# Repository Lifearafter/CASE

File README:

# C.A.S.E

Welcome to the Compact Antenna Experimenter System Project repository! This project focuses on providing the necessary code and documentation to create a fully functional and electrically viable CubeSat. In this repository, you will find the software and firmware that drive the electrical components of a CubeSat, ensuring its proper functionality in space.

## Table of Contents

- Introduction
- Getting Started
- Project Structure
- Dependencies
- Contributing
- License

## Introduction

CubeSats are miniaturized satellites that have become increasingly popular for space exploration and scientific research due to their small size, cost-effectiveness, and modular design. This project focuses specifically on the electrical aspects of a CubeSat, excluding any mechanical components.

The key objectives of this project include:

- **Power Management:** Efficiently manage power resources to ensure the CubeSat's continuous operation in space.

- **Communication Systems:** Implement reliable communication protocols for data transmission between the CubeSat and ground control.

- **Sensor Integration:** Integrate and interface various sensors to gather data for scientific or mission-specific purposes.

- **Onboard Computer Systems:** Develop the necessary software for the CubeSat's onboard computer to execute mission tasks and handle data.

- **Fault Tolerance:** Implement mechanisms to handle errors and faults to ensure the CubeSat's robustness in harsh space environments.

## Getting Started

To get started with the CubeSatellite Electrical System Project, follow these steps:

1. **Clone the Repository:**

```
bash
Copy code
git clone https://github.com/your-username/cubesatellite-electrical.git
```

2. **Navigate to the Project Directory:**

```
bash
Copy code
cd cubesatellite-electrical
```

## Explore the Code:

Review the codebase to understand the implementation details and structure.

## Set Up Development Environment:

Follow the instructions in the docs/setup.md document to set up your development environment.

## Contribute:

If you would like to contribute to the project, please follow the guidelines outlined in the Contributing section.

## Project Structure

The project is organized into the following directories:

- src: Contains the source code for the CubeSat's electrical systems.
- docs: Documentation files, including setup instructions and usage guidelines.
- tests: Test cases for ensuring the reliability and functionality of the code.
- inc: Contains all the header files for the project.

## Dependencies

Ensure that you have the following dependencies installed in your development environment:
**Not yet listed**

## License

This project is licensed under the MIT License. Feel free to use, modify, and distribute the code for your CubeSat projects.

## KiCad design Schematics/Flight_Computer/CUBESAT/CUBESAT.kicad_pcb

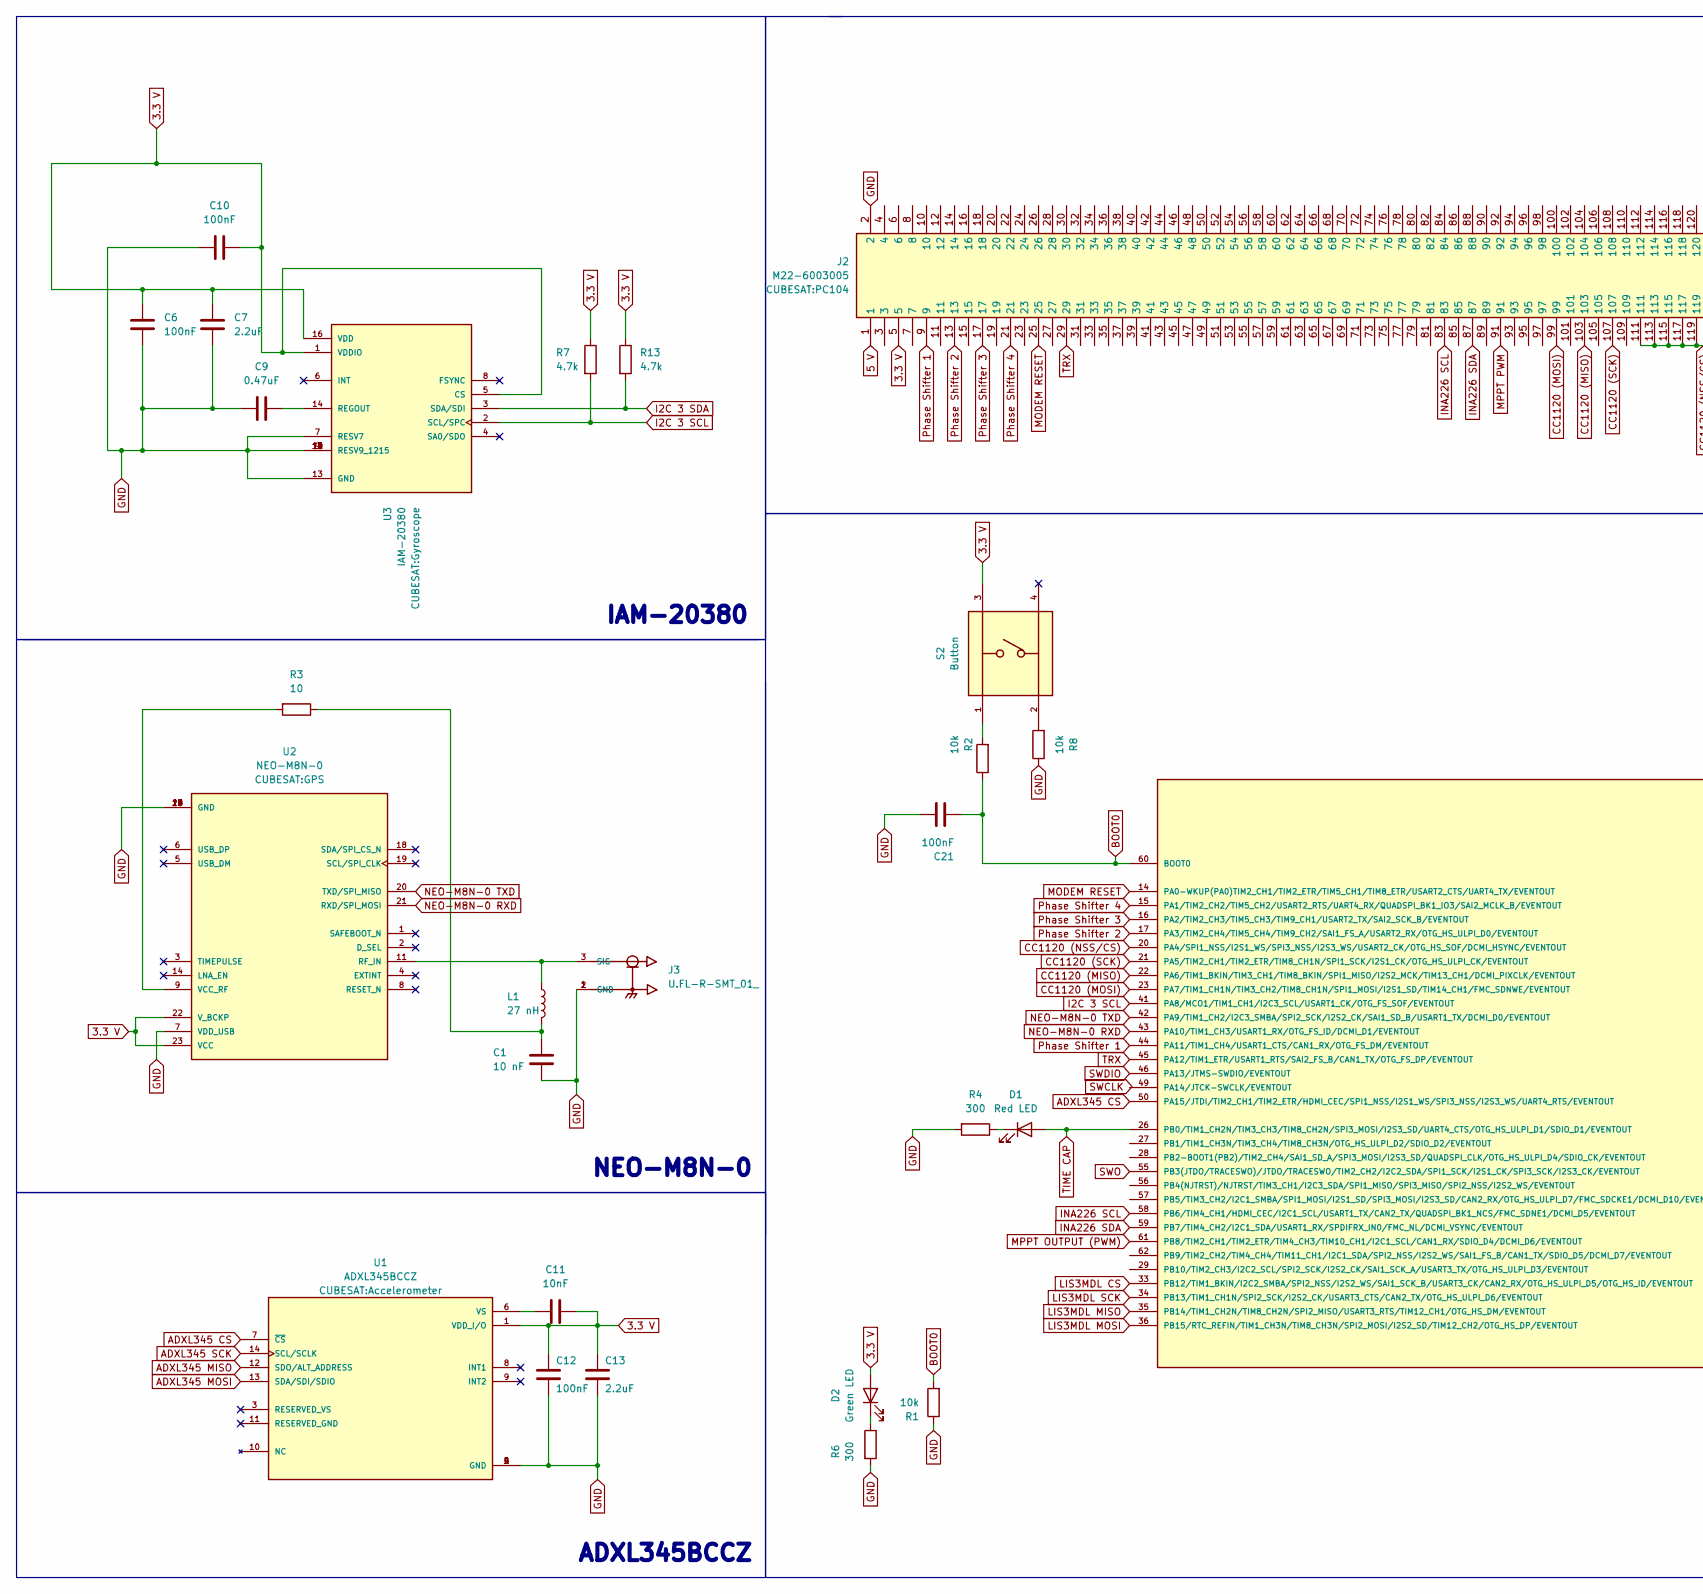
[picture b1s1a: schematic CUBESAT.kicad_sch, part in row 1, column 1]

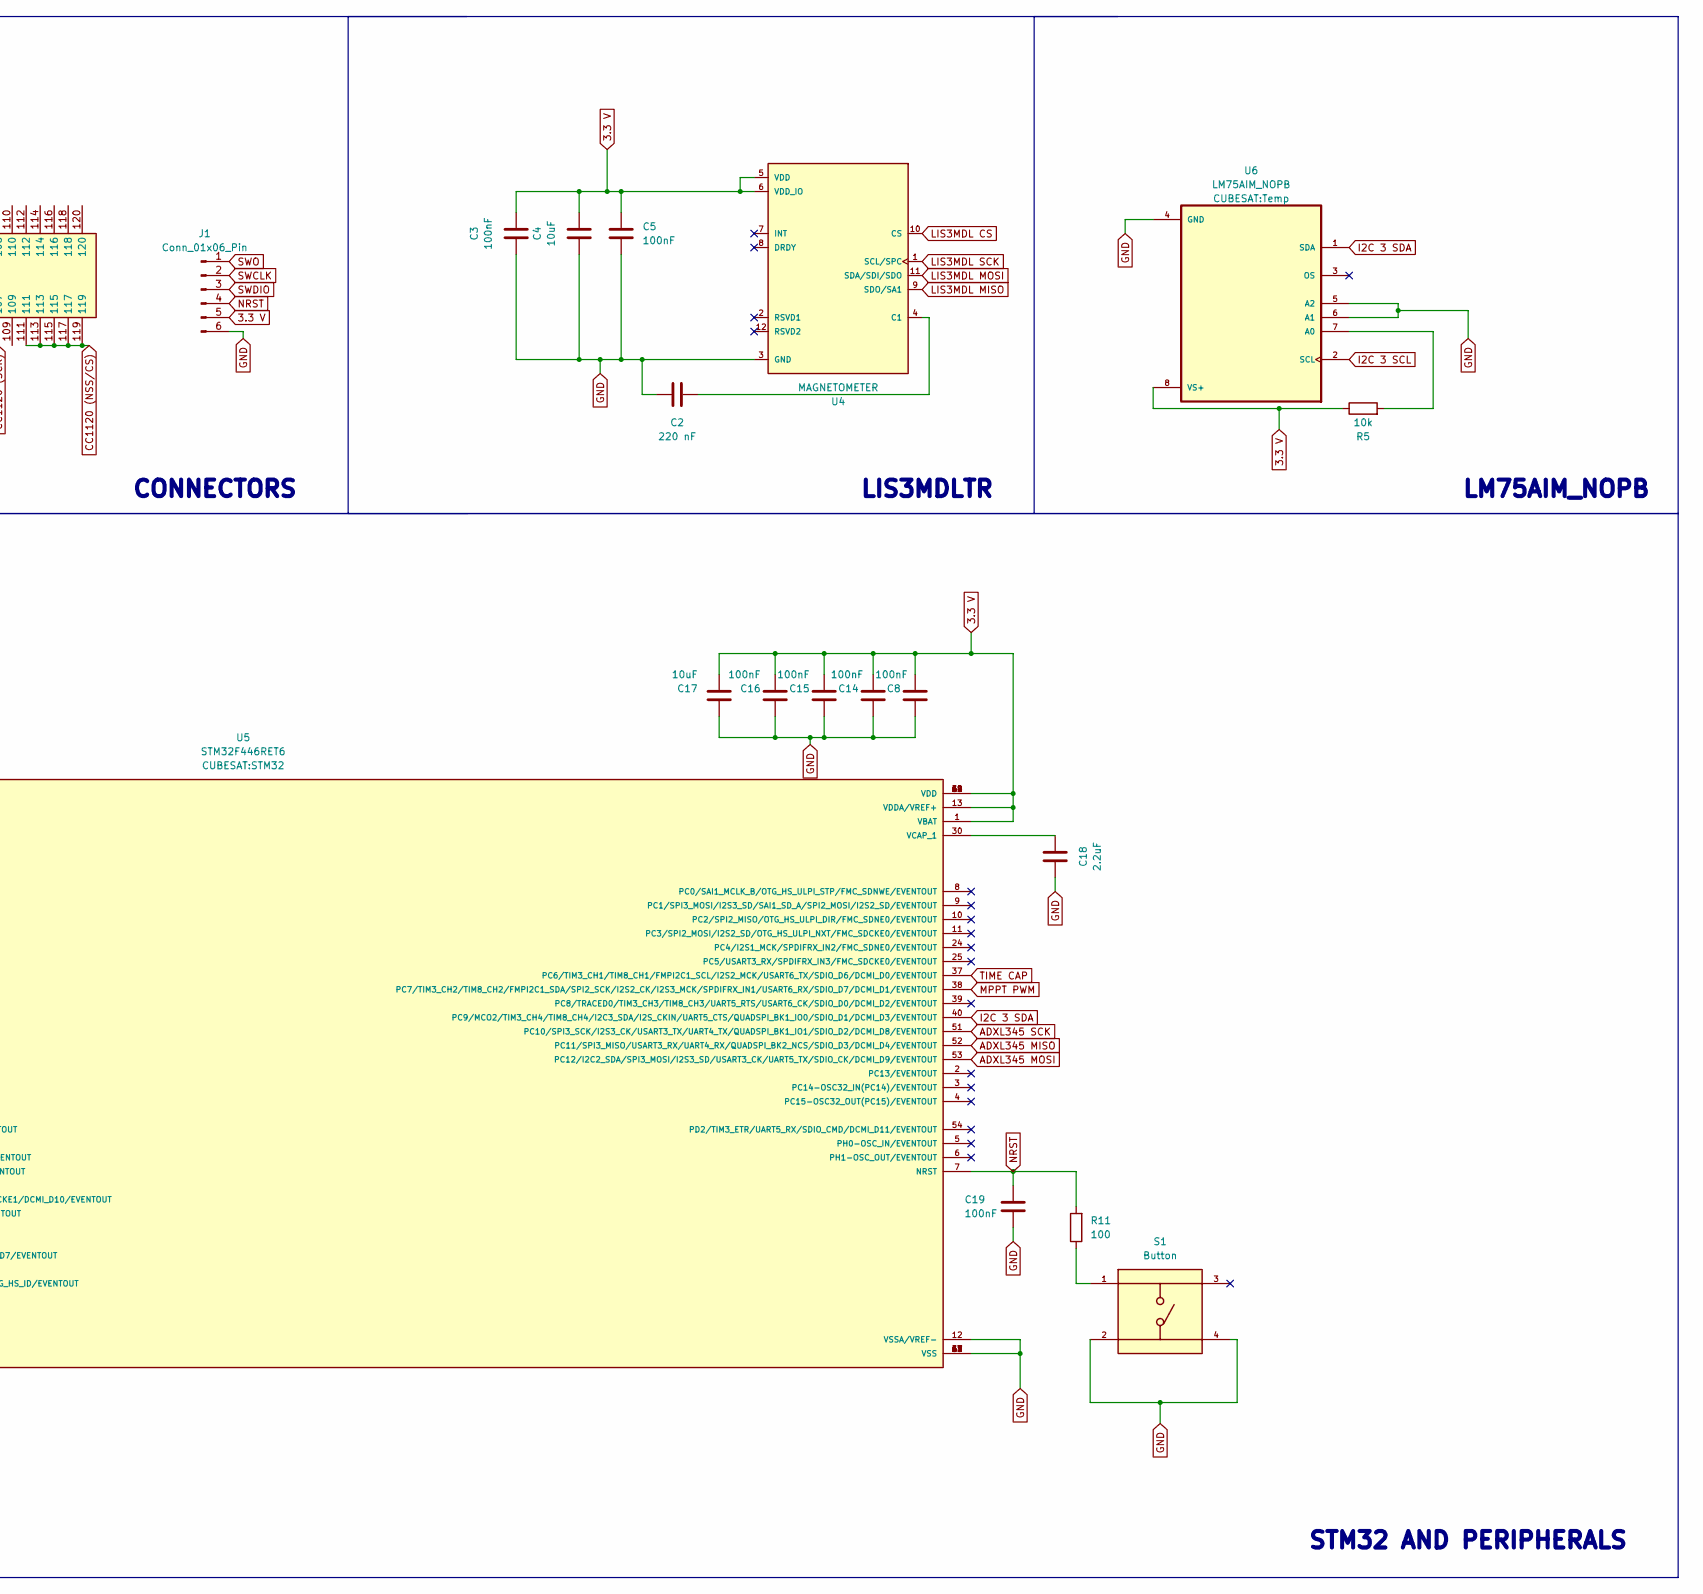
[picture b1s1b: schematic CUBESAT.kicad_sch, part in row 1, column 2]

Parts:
C1: 10 nF; Capacitor10nf
C2: 220 nF; Capacitor220nf
C3, C5, C6, C8, C10, C12, C14, C15, C16, C19, C21: 100nF; Capacitor100nf
C4, C17: 10uF; Capacitor10uf
C7, C13, C18: 2.2uF; Capacitor2-2uf
C9: 0.47uF; Capacitor0-47uf
C11: 10nF; Capacitor10nf
D1: Red LED
D2: Green LED
J1: Conn_01x06_Pin; 6 Pin Connector
J2: M22-6003005; PC104; Manufacturer_Part_Number M22-6003005
J3: U.FL-R-SMT_01_; UFL
L1: 27 nH; Inductor27nH
R1, R2, R5, R8: 10k; Resistor10kO
R3: 10; Resistor10O
R4, R6: 300; Resistor300O
R7, R13: 4.7k; Resistor4.7kO
R11: 100; Reistor100O
S1, S2: Button
U1: ADXL345BCCZ; Accelerometer; PARTREV G
U2: NEO-M8N-0; GPS; PARTREV R04
U3: IAM-20380; Gyroscope
U4: MAGNETOMETER
U5: STM32F446RET6; STM32; PARTREV 6
U6: LM75AIM_NOPB; Temp

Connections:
3.3 V: C3.2, C4.2, C5.2, C6.1, C7.1, C8.1, C10.2, C11.2, C12.1, C13.1, C14.1, C15.1, C16.1, C17.1, D2.2 (A), J1.5, J2.5, R5.1, R7.1, R13.1, S2.3, U1.1 (VDD_I/O), U2.22 (V_BCKP), U2.23 (VCC), U3.1 (VDDIO), U3.5 (CS), U3.16 (VDD), U4.5 (VDD), U4.6 (VDD_IO), U5.1 (VBAT), U5.13 (VDDA/VREF+), U5.19 (VDD), U5.32 (VDD), U5.48 (VDD), U5.64 (VDD), U6.8 (VS+)
5 V: J2.1
ADXL345 CS: U1.7 (~CS), U5.50 (PA15/JTDI/TIM2_CH1/TIM2_ETR/HDMI_CEC/SP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)
ADXL345 MISO: U1.12 (SDO/ALT_ADDRESS), U5.52 (PC11/SPI3_MISO/USART3_RX/UART4_RX/QUADS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)
ADXL345 MOSI: U1.13 (SDA/SDI/SDIO), U5.53 (PC12/I2C2_SDA/SPI3_MOSI/I2S3_SD/USART3_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)
ADXL345 SCK: U1.14 (SCL/SCLK), U5.51 (PC10/SPI3_SCK/I2S3_CK/USART3_TX/UART4_T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)
BOOT0: C21.2, R1.2, R2.1, U5.60 (BOOT0)
CC1120 (MISO): J2.103, U5.22 (PA6/TIM1_BKIN/TIM3_CH1/TIM8_BKIN/SPI1_M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)
CC1120 (MOSI): J2.99, U5.23 (PA7/TIM1_CH1N/TIM3_CH2/TIM8_CH1N/SPI1_M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)
CC1120 (NSS/CS): J2.111, J2.113, J2.115, J2.117, J2.119, U5.20 (PA4/SPI1_NSS/I2S1_WS/SPI3_NSS/I2S3_WS/U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)
CC1120 (SCK): J2.107, U5.21 (PA5/TIM2_CH1/TIM2_ETR/TIM8_CH1N/SPI1_SC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)
GND: C1.2, C2.1, C3.1, C4.1, C5.1, C6.2, C7.2, C8.2, C9.2, C10.1, C12.2, C13.2, C14.2, C15.2, C16.2, C17.2, C18.1, C19.2, C21.1, J1.6, J2.2, J3.1 (GND), J3.2 (GND), R1.1, R4.2, R6.2, R8.1, S1.2, S1.4, U1.2 (GND), U1.4 (GND), U1.5 (GND), U2.7 (VDD_USB), U2.10 (GND), U2.12 (GND), U2.13 (GND), U2.24 (GND), U3.7 (RESV7), U3.9 (RESV9_1215), U3.10 (RESV9_1215), U3.11 (RESV9_1215), U3.12 (RESV9_1215), U3.13 (GND), U3.15 (RESV9_1215), U4.3 (GND), U5.12 (VSSA/VREF-), U5.18 (VSS), U5.31 (VSS), U5.47 (VSS), U5.63 (VSS), U6.4 (GND), U6.5 (A2), U6.6 (A1)
I2C 3 SCL: R7.2, U3.2 (SCL/SPC), U5.41 (PA8/MCO1/TIM1_CH1/I2C3_SCL/USART1_CK/OT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), U6.2 (SCL)
I2C 3 SDA: R13.2, U3.3 (SDA/SDI), U5.40 (PC9/MCO2/TIM3_CH4/TIM8_CH4/I2C3_SDA/I2S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), U6.1 (SDA)
INA226 SCL: J2.83, U5.58 (PB6/TIM4_CH1/HDMI_CEC/I2C1_SCL/USART1_T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)
INA226 SDA: J2.87, U5.59 (PB7/TIM4_CH2/I2C1_SDA/USART1_RX/SPDIFRX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)
LIS3MDL CS: U4.10 (CS), U5.33 (PB12/TIM1_BKIN/I2C2_SMBA/SPI2_NSS/I2S2_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)
LIS3MDL MISO: U4.9 (SDO/SA1), U5.35 (PB14/TIM1_CH2N/TIM8_CH2N/SPI2_MISO/USAR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)
LIS3MDL MOSI: U4.11 (SDA/SDI/SDO), U5.36 (PB15/RTC_REFIN/TIM1_CH3N/TIM8_CH3N/SPI2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)
LIS3MDL SCK: U4.1 (SCL/SPC), U5.34 (PB13/TIM1_CH1N/SPI2_SCK/I2S2_CK/USART3_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)
MODEM RESET: J2.25, U5.14 (PA0-WKUP(PA0)TIM2_CH1/TIM2_ETR/TIM5_CH1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)
MPPT OUTPUT (PWM): U5.61 (PB8/TIM2_CH1/TIM2_ETR/TIM4_CH3/TIM10_CH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)
MPPT PWM: J2.91, U5.38 (PC7/TIM3_CH2/TIM8_CH2/FMPI2C1_SDA/SPI2_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)
NEO-M8N-0 RXD: U2.21 (RXD/SPI_MOSI), U5.43 (PA10/TIM1_CH3/USART1_RX/OTG_FS_ID/DCMI_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)
NEO-M8N-0 TXD: U2.20 (TXD/SPI_MISO), U5.42 (PA9/TIM1_CH2/I2C3_SMBA/SPI2_SCK/I2S2_CK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)
NRST: C19.1, J1.4, R11.2, U5.7 (NRST)
unnamed: C1.1, L1.2, R3.1
unnamed: D1.1 (K), R4.1
unnamed: D2.1 (K), R6.1
unnamed: J3.3 (SIG), L1.1, U2.11 (RF_IN)
unnamed: R2.2, S2.1
unnamed: R8.2, S2.2
unnamed: R11.1, S1.1
unnamed: C11.1, U1.6 (VS)
unnamed: R3.2, U2.9 (VCC_RF)
unnamed: C9.1, U3.14 (REGOUT)
unnamed: C2.2, U4.4 (C1)
unnamed: C18.2, U5.30 (VCAP_1)
unnamed: R5.2, U6.7 (A0)
Phase Shifter 1: J2.9, U5.44 (PA11/TIM1_CH4/USART1_CTS/CAN1_RX/OTG_FS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)
Phase Shifter 2: J2.13, U5.17 (PA3/TIM2_CH4/TIM5_CH4/TIM9_CH2/SAI1_FS_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)
Phase Shifter 3: J2.17, U5.16 (PA2/TIM2_CH3/TIM5_CH3/TIM9_CH1/USART2_T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)
Phase Shifter 4: J2.21, U5.15 (PA1/TIM2_CH2/TIM5_CH2/USART2_RTS/UART4_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)
SWCLK: J1.2
SWDIO: J1.3, U5.46 (PA13/JTMS-SWDIO/EVENTOUT)
SWO: J1.1, U5.55 (PB3(JTDO/TRACESWO)/JTDO/TRACESWO/TIM2_C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)
TIME CAP: D1.2 (A), U5.26 (PB0/TIM1_CH2N/TIM3_CH3/TIM8_CH2N/SPI3_M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), U5.37 (PC6/TIM3_CH1/TIM8_CH1/FMPI2C1_SCL/I2S2_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)
TRX: J2.29, U5.45 (PA12/TIM1_ETR/USART1_RTS/SAI2_FS_B/CAN1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)

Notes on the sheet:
ADXL345BCCZ
STM32 AND PERIPHERALS
IAM-20380
LIS3MDLTR
CONNECTORS
LM75AIM_NOPB
NEO-M8N-0

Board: 2 copper layers, 44 parts (0 on the bottom side), 45 nets, no tracks yet.

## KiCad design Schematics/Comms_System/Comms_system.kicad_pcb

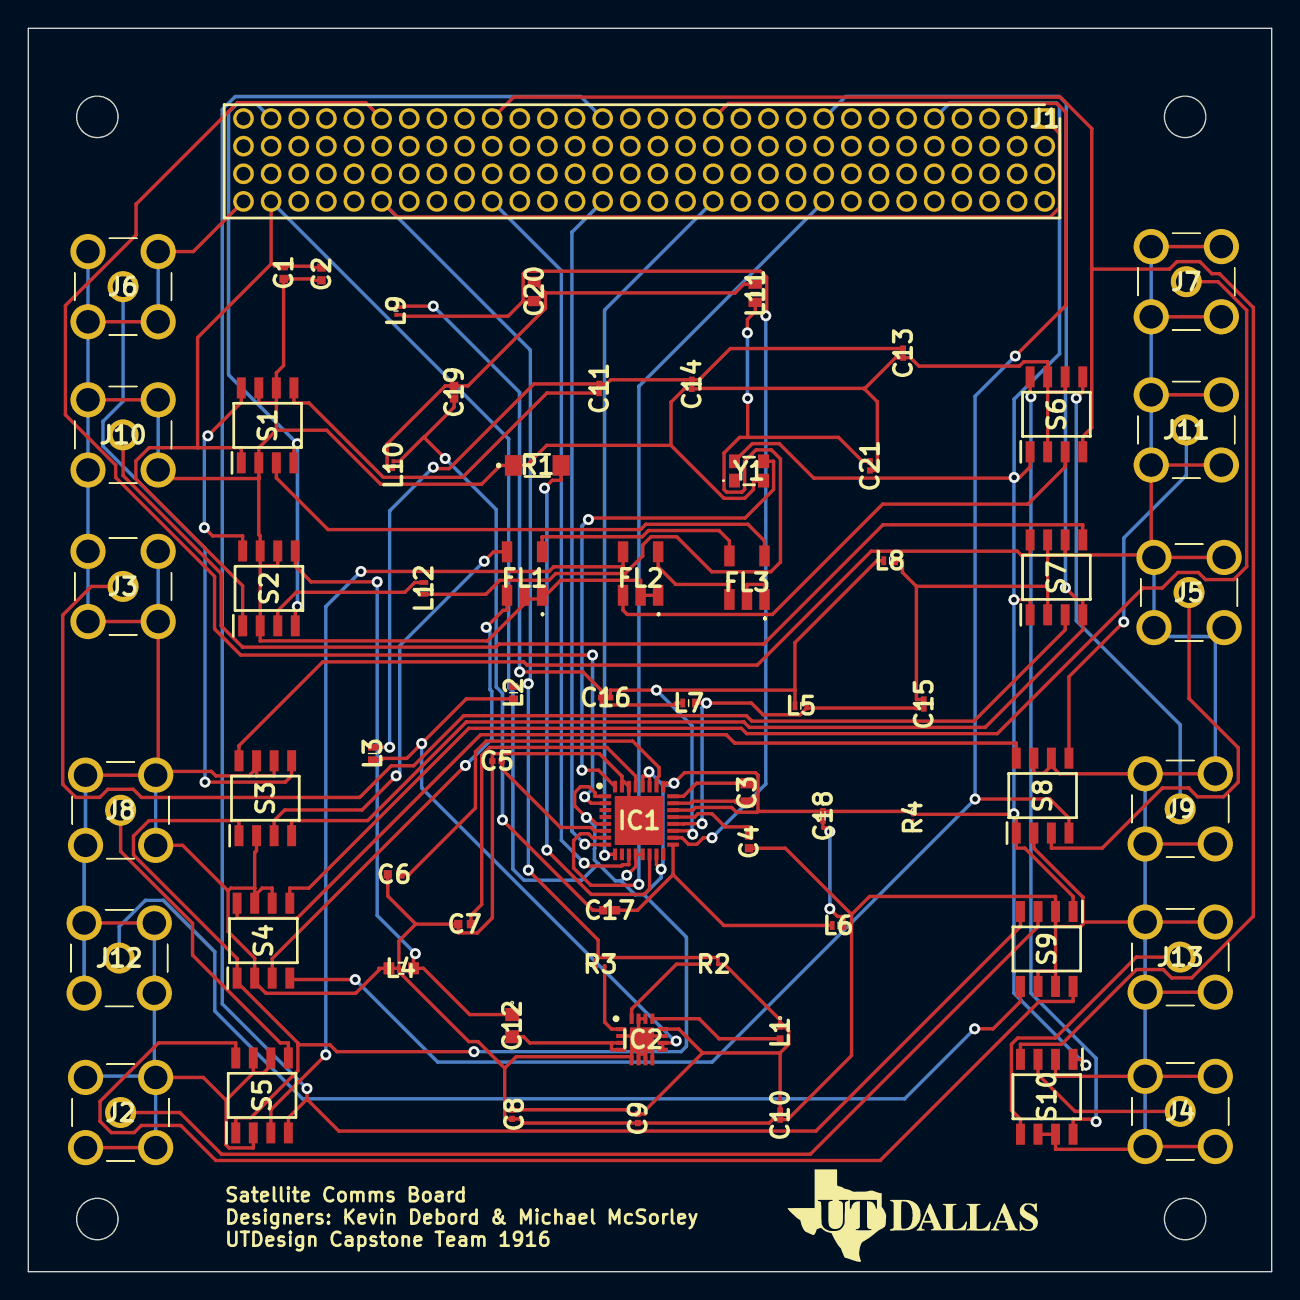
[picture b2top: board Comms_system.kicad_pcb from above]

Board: 2 copper layers, 90.0 x 90.0 mm, 66 parts (0 on the bottom side), 64 nets.

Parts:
C1, C2, C6, C7: GRM155R61C473JA01J; CAPC1005X55N
C3: GCD188R71H392KA01J; CAPC1608X90N
C4: C0402C103K1RACAUTO; CAPC1005X55N
C5: GRT033R61A224KE01D; CAPC0603X33N
C8, C11: GRM033R71C101JA01D; CAPC0603X33N
C9, C10: EMK063AC6104KP-F; CAPC0603X35N
C12: C0603C200K8HACTU; C0603
C13: GRM0335C1H4R3WA01D; CAPC0603X33N
C14: GRT0335C1ER22WA02D; CAPC0603X33N
C15, C16: GRM0335C1H5R1DA01D; CAPC0603X33N
C17: AC0402JRNPO9BN390; CAPC1005X55N
C18: C0201C560J3GACTU; C0201
C19: GJM1555C1H2R2CB01D; CAPC1005X55N
C20: GRM1885C1H512JA01D; CAPC1608X90N
C21: GRM0335C1H6R2DA01D; CAPC0603X33N
FL1, FL2, FL3: SBTC-2-10LX+; SBTC210LX
IC1: CC1120RHBR; QFN50P500X500X100-33N-D
IC2: GRF5504; QFN50P300X300X90-17N
J1: M22-6003005; RHDR120W55P200_4X30_6020X800X935P
J2, J3, J4, J5, J6, J7, J8, J9, J10, J11, J12, J13: 132134
L1: MLG1005S5N6ST000; MLG1005
L2, L3: LQG15WH3N0B02D; LQW15CNR20J00B
L4: B82496C3829J; INDC1608X90N
L5, L6: LQG15HS56NJ02D; LQG15WH0N7B02D
L7, L8: LQG15HH27NJ02D; LQG15WH0N7B02D
L9, L10: LQP03TN15NH02D; LQP03TG3N1B02D
L11: LQW18AN43NJ0ZD; LQW18AS10NG0CD
L12: LQG15HH22NJ02D; LQG15WH0N7B02D
R1: ERA-8VEB5602V; ERA8KEB1004V
R2: ERJ-1GJF6801C; ERJ1GJJ2R4C
R3: ERJ-1GJF3301C; ERJ1GJJ2R4C
R4: ERJ-XGNJ180Y; ERJXG__01005_
S1, S2, S3, S4, S5, S6, S7, S8, S9, S10: SA630D_01,112; SOIC127P600X175-8N
Y1: TG2520SMN_32.0000M-ECGNNM0; TG2520SMN320000MECGNNM0

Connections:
+3.3V: C1.2, C2.2, C18.1, IC1.1 (VDD_GUARD), IC1.5 (DVDD_1), IC1.12 (DVDD_2), IC1.13 (AVDD_IF), IC1.15 (AVDD_RF), IC1.22 (AVDD_SYNTH1), IC1.25 (AVDD_PFD_CHP), IC1.27 (AVDD_SYNTH2), IC1.28 (AVDD_XOSC), J1.5, J1.119, R4.1, S1.1 (VDD), S2.1 (VDD), S3.1 (VDD), S4.1 (VDD), S5.1 (VDD), S6.1 (VDD), S7.1 (VDD), S8.1 (VDD), S9.1 (VDD), S10.1 (VDD), Y1.4 (VCC)
+5V: C8.1, C9.1, C10.1, IC2.12 (BIAS), J1.1, J1.115, L1.1, L2.1, R2.1, R3.1
/Amplifier_Array/Signal_1_In: C12.1, L4.1, S2.5 (OUT2)
/Amplifier_Array/Signal_1_Out: C11.1, S1.5 (OUT2)
/CC1120_TX_RX_Switch: C20.2, IC1.18 (TRX_SW), L9.2
/Phase_Shifter_Array/Signal_In_1: FL1.4 (PORT_2), S3.3 (INPUT)
/Phase_Shifter_Array/Signal_In_2: FL1.3 (PORT_1), S4.3 (INPUT)
/Phase_Shifter_Array/Signal_In_3: FL2.4 (PORT_2), S5.3 (INPUT)
/Phase_Shifter_Array/Signal_In_4: FL2.3 (PORT_1), S6.3 (INPUT)
/RF_CC1120_In_LNA_N_Con: C15.1, IC1.20 (LNA_N), L5.2, L7.1
/RF_CC1120_In_LNA_P_Con: C16.1, IC1.19 (LNA_P), L5.1, L8.2
/RF_CC1120_Out_Con: C17.1, IC1.17 (PA), L6.2
/RF_End_Con_1: J3.1, S7.3 (INPUT)
/RF_End_Con_2: J5.1, S8.3 (INPUT)
/RF_End_Con_3: J2.1, S9.3 (INPUT)
/RF_End_Con_4: J4.1, S10.3 (INPUT)
/RF_Manifold_Con: FL3.6 (SUM_PORT), S1.3 (INPUT)
/RF_Matched_Out: L12.2, S2.3 (INPUT)
CSN_CC1120: IC1.11 (CSN), J1.111
GND: C1.1, C2.1, C4.2, C5.2, C6.1, C7.1, C8.2, C9.2, C10.2, C13.2, C14.2, C15.2, C21.1, FL1.1 (GROUND_1), FL1.2 (GROUND_2), FL2.1 (GROUND_1), FL2.2 (GROUND_2), IC1.30 (XOSC_Q1), IC1.31 (XOSC_Q2), IC1.33 (EPAD), IC2.2 (GND/NC_1), IC2.5 (GND/NC_2), IC2.6 (GND/NC_3), IC2.7 (GND/NC_4), IC2.8 (GND/NC_5), IC2.11 (GND/NC_6), IC2.14 (GND/NC_7), IC2.15 (GND/NC_8), IC2.17 (GND), J1.120, J2.2, J2.3, J2.4, J2.5, J3.2, J3.3, J3.4, J3.5, J4.2, J4.3, J4.4, J4.5, J5.2, J5.3, J5.4, J5.5, J6.2, J6.3, J6.4, J6.5, J7.2, J7.3, J7.4, J7.5, J8.2, J8.3, J8.4, J8.5, J9.2, J9.3, J9.4, J9.5, J10.2, J10.3, J10.4, J10.5, J11.2, J11.3, J11.4, J11.5, J12.2, J12.3, J12.4, J12.5, J13.2, J13.3, J13.4, J13.5, L4.2, L8.1, R1.1, S1.2 (GND_1), S1.6 (GND_2), S1.7 (AC_GND), S2.2 (GND_1), S2.6 (GND_2), S2.7 (AC_GND), S3.2 (GND_1), S3.6 (GND_2), S3.7 (AC_GND), S4.2 (GND_1), S4.6 (GND_2), S4.7 (AC_GND), S5.2 (GND_1), S5.6 (GND_2), S5.7 (AC_GND), S6.2 (GND_1), S6.6 (GND_2), S6.7 (AC_GND), S7.2 (GND_1), S7.6 (GND_2), S7.7 (AC_GND), S8.2 (GND_1), S8.6 (GND_2), S8.7 (AC_GND), S9.2 (GND_1), S9.6 (GND_2), S9.7 (AC_GND), S10.2 (GND_1), S10.6 (GND_2), S10.7 (AC_GND), Y1.2 (GND)
GPIO_Lane_1: J1.9, S3.4 (ENCH1), S7.4 (ENCH1)
GPIO_Lane_2: J1.13, S4.4 (ENCH1), S8.4 (ENCH1)
GPIO_Lane_3: J1.17, S5.4 (ENCH1), S9.4 (ENCH1)
GPIO_Lane_4: J1.21, S6.4 (ENCH1), S10.4 (ENCH1)
GPIO_Lane_5: IC1.2 (RESET_N), J1.25
GPIO_Lane_6: J1.29, S1.4 (ENCH1), S2.4 (ENCH1)
unnamed: C11.2, C13.1, C14.1, L3.2
unnamed: C16.2, L7.2, L9.1
unnamed: C17.2, C19.2, L10.1
unnamed: C18.2, L6.1, R4.2
unnamed: C19.1, C20.1, L10.2, L11.1
unnamed: C21.2, L11.2, L12.1
unnamed: FL1.6 (SUM_PORT), FL3.4 (PORT_2)
unnamed: FL2.6 (SUM_PORT), FL3.3 (PORT_1)
unnamed: FL3.1 (GROUND_1), FL3.2 (GROUND_2)
unnamed: C5.1, IC1.6 (DCPL)
unnamed: C6.2, IC1.26 (DCPL_PFD_CHP)
unnamed: C4.1, IC1.21 (DCPL_VCO)
unnamed: C7.2, IC1.29 (DCPL_XOSC)
unnamed: IC1.32 (EXT_XOSC), Y1.3 (OUT)
unnamed: C3.1, IC1.23 (LPF0)
unnamed: C3.2, IC1.24 (LPF1)
unnamed: IC1.14 (RBIAS), R1.2
unnamed: C12.2, IC2.3 (RF_IN_1), IC2.4 (RF_IN_2)
unnamed: IC2.9 (RF_OUT/VCC2_1), IC2.10 (RF_OUT/VCC2_2), L2.2, L3.1
unnamed: IC2.13 (VCC1), L1.2
unnamed: IC2.1 (VENABLE1), R3.2
unnamed: IC2.16 (VENABLE2), R2.2
unnamed: S1.8 (OUT1), S2.8 (OUT1)
unnamed: S3.8 (OUT1), S7.8 (OUT1)
unnamed: J6.1, S3.5 (OUT2)
unnamed: S4.8 (OUT1), S8.8 (OUT1)
unnamed: J7.1, S4.5 (OUT2)
unnamed: S5.8 (OUT1), S9.8 (OUT1)
unnamed: J8.1, S5.5 (OUT2)
unnamed: J9.1, S6.5 (OUT2)
unnamed: J10.1, S7.5 (OUT2)
unnamed: J11.1, S8.5 (OUT2)
unnamed: J12.1, S9.5 (OUT2)
unnamed: S6.8 (OUT1), S10.8 (OUT1)
unnamed: J13.1, S10.5 (OUT2)
SPI_CLK: IC1.8 (SCLK), J1.107
SPI_MISO: IC1.9 (SO_(GPIO1)), J1.103
SPI_MOSI: IC1.7 (SI), J1.99

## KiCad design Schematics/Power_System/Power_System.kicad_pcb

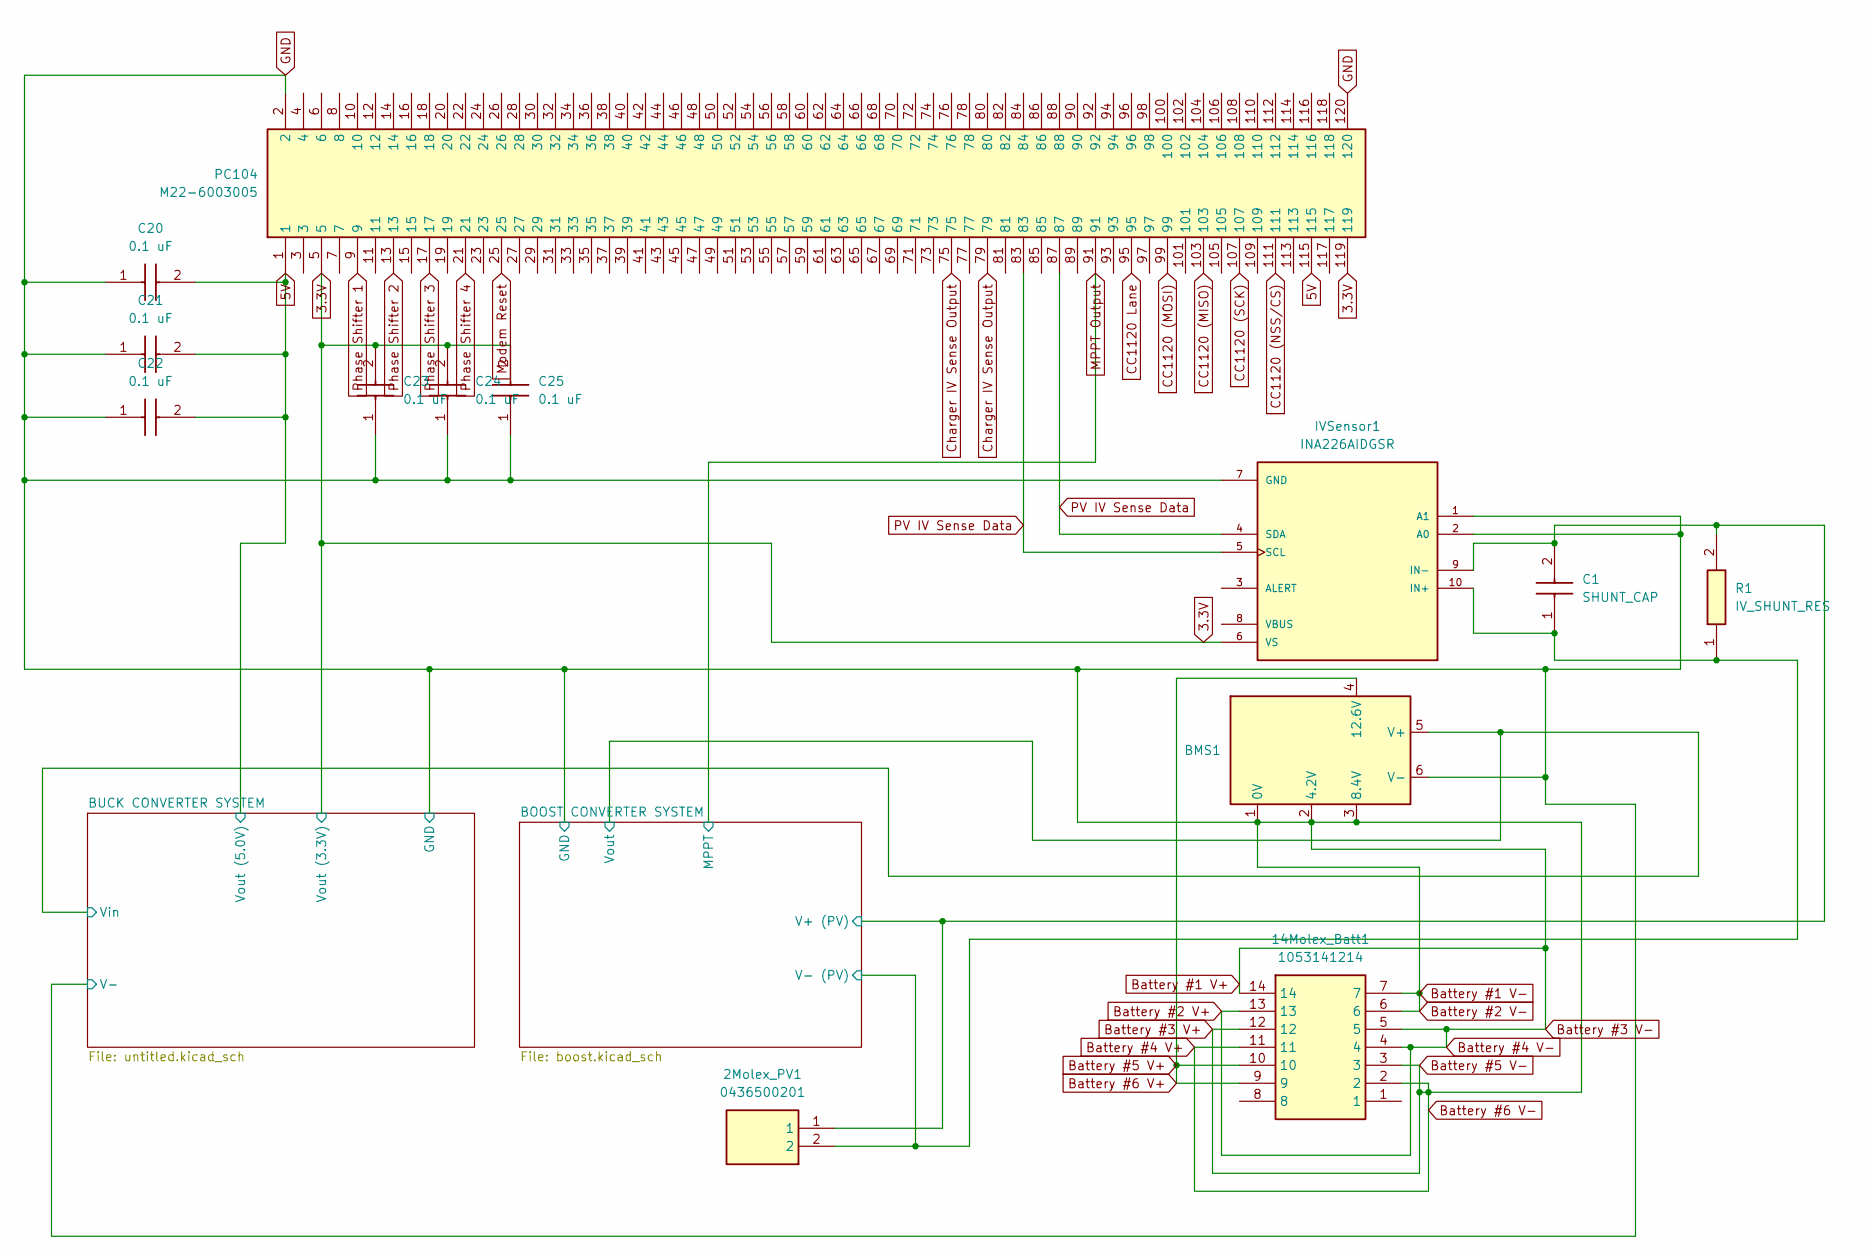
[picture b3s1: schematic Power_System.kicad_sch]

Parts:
2Molex_PV1: 0436500201; Manufacturer_Part_Number 0436500201; Mouser Part Number N/A
14Molex_Batt1: 1053141214; 105314YY14; Manufacturer_Part_Number 1053141214
BMS1: BMS
C1: SHUNT_CAP; C0805; Manufacturer_Part_Number C0805C102F5GACAUTO; Mouser Part Number 80-C0805C102F5GAUTO
C20, C21, C22, C23, C24, C25: 0.1 uF; Manufacturer_Part_Number C0603C104K1RACAUTO; Mouser Part Number 80-C0603C104K1RAUTO
IVSensor1: INA226AIDGSR; Powcur
PC104: M22-6003005; PC104; Manufacturer_Part_Number M22-6003005
R1: IV_SHUNT_RES; RESM11670X254N; Manufacturer_Part_Number WSR21R000FEA; Mouser Part Number 71-WSR21R000FEA

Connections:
3.3V: C23.2, C24.2, C25.2, IVSensor1.6 (VS), PC104.5, PC104.119; also elsewhere on the board
5V: C20.2, C21.2, C22.2, PC104.1, PC104.115; also elsewhere on the board
/BOOST CONVERTER SYSTEM/V+ (PV): 2Molex_PV1.1, C1.2, IVSensor1.9 (IN-), R1.2; also elsewhere on the board
/BOOST CONVERTER SYSTEM/Vout: BMS1.5 (V+); also elsewhere on the board
Battery #1 V+: 2Molex_PV1.2, 14Molex_Batt1.2, 14Molex_Batt1.3, 14Molex_Batt1.4, 14Molex_Batt1.5, 14Molex_Batt1.6, 14Molex_Batt1.7, 14Molex_Batt1.11, 14Molex_Batt1.12, 14Molex_Batt1.13, 14Molex_Batt1.14, BMS1.1 (0V), BMS1.2 (4.2V), BMS1.3 (8.4V), BMS1.6 (V-), C1.1, C20.1, C21.1, C22.1, C23.1, C24.1, C25.1, IVSensor1.1 (A1), IVSensor1.2 (A0), IVSensor1.7 (GND), IVSensor1.10 (IN+), PC104.2, PC104.120, R1.1; also elsewhere on the board
Battery #5 V+: 14Molex_Batt1.9, 14Molex_Batt1.10, BMS1.4 (12.6V)
CC1120 (MISO): PC104.103
CC1120 (MOSI): PC104.99
CC1120 (NSS/CS): PC104.111
CC1120 (SCK): PC104.107
CC1120 Lane: PC104.95
Charger IV Sense Output: PC104.75, PC104.79
MPPT Output: PC104.91; also elsewhere on the board
Modem Reset: PC104.25
PV IV Sense Data: IVSensor1.4 (SDA), IVSensor1.5 (SCL), PC104.83, PC104.87
Phase Shifter 1: PC104.9
Phase Shifter 2: PC104.13
Phase Shifter 3: PC104.17
Phase Shifter 4: PC104.21

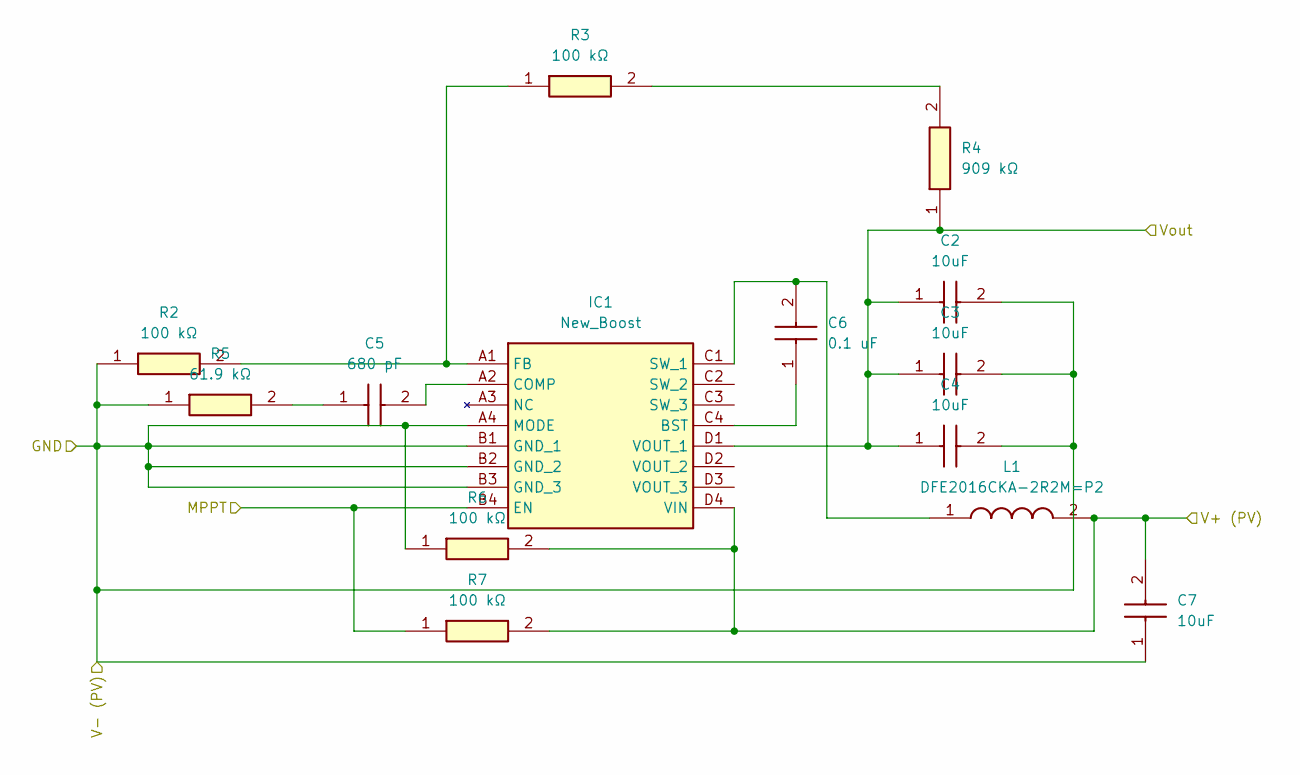
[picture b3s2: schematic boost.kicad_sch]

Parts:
C2, C3, C4, C7: 10uF; Manufacturer_Part_Number GRM188R61E106KA73D; Mouser Part Number 81-GRM188R61E106KA3D
C5: 680 pF; Manufacturer_Part_Number GCM1555C1H681FA16D; Mouser Part Number 81-GCM1555C1H681FA6D
C6: 0.1 uF; Manufacturer_Part_Number C0603C104K1RACAUTO; Mouser Part Number 80-C0603C104K1RAUTO
IC1: New_Boost; Manufacturer_Part_Number TPS61372YKBT; Mouser Part Number 595-TPS61372YKBT
L1: DFE2016CKA-2R2M=P2; DFE2016CKA1R0MP2; Manufacturer_Part_Number DFE2016CKA-2R2M=P2; Mouser Part Number 81-DFE2016CKA2R2M=P2
R2, R3, R6, R7: 100 kΩ; RESC1608X55N; Manufacturer_Part_Number MCT0603MG1003BP500; Mouser Part Number 594-MCT0603MG1003BP5
R4: 909 kΩ; Manufacturer_Part_Number RC0402FR-07909KL; Mouser Part Number 603-RC0402FR-07909KL
R5: 61.9 kΩ; Manufacturer_Part_Number ERA-3VEB6192V

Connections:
/BOOST CONVERTER SYSTEM/V+ (PV): C7.2, IC1.D4 (VIN), L1.2, R6.2, R7.2; also elsewhere on the board
/BOOST CONVERTER SYSTEM/Vout: C2.1, C3.1, C4.1, IC1.D1 (VOUT_1), R4.1; also elsewhere on the board
Battery #1 V+: C2.2, C3.2, C4.2, C7.1, IC1.A4 (MODE), IC1.B1 (GND_1), IC1.B2 (GND_2), IC1.B3 (GND_3), R2.1, R5.1, R6.1; also elsewhere on the board
MPPT Output: IC1.B4 (EN), R7.1; also elsewhere on the board
unnamed: C5.1, R5.2
unnamed: C6.1, IC1.C4 (BST)
unnamed: C5.2, IC1.A2 (COMP)
unnamed: IC1.A1 (FB), R2.2, R3.1
unnamed: C6.2, IC1.C1 (SW_1), L1.1
unnamed: R3.2, R4.2

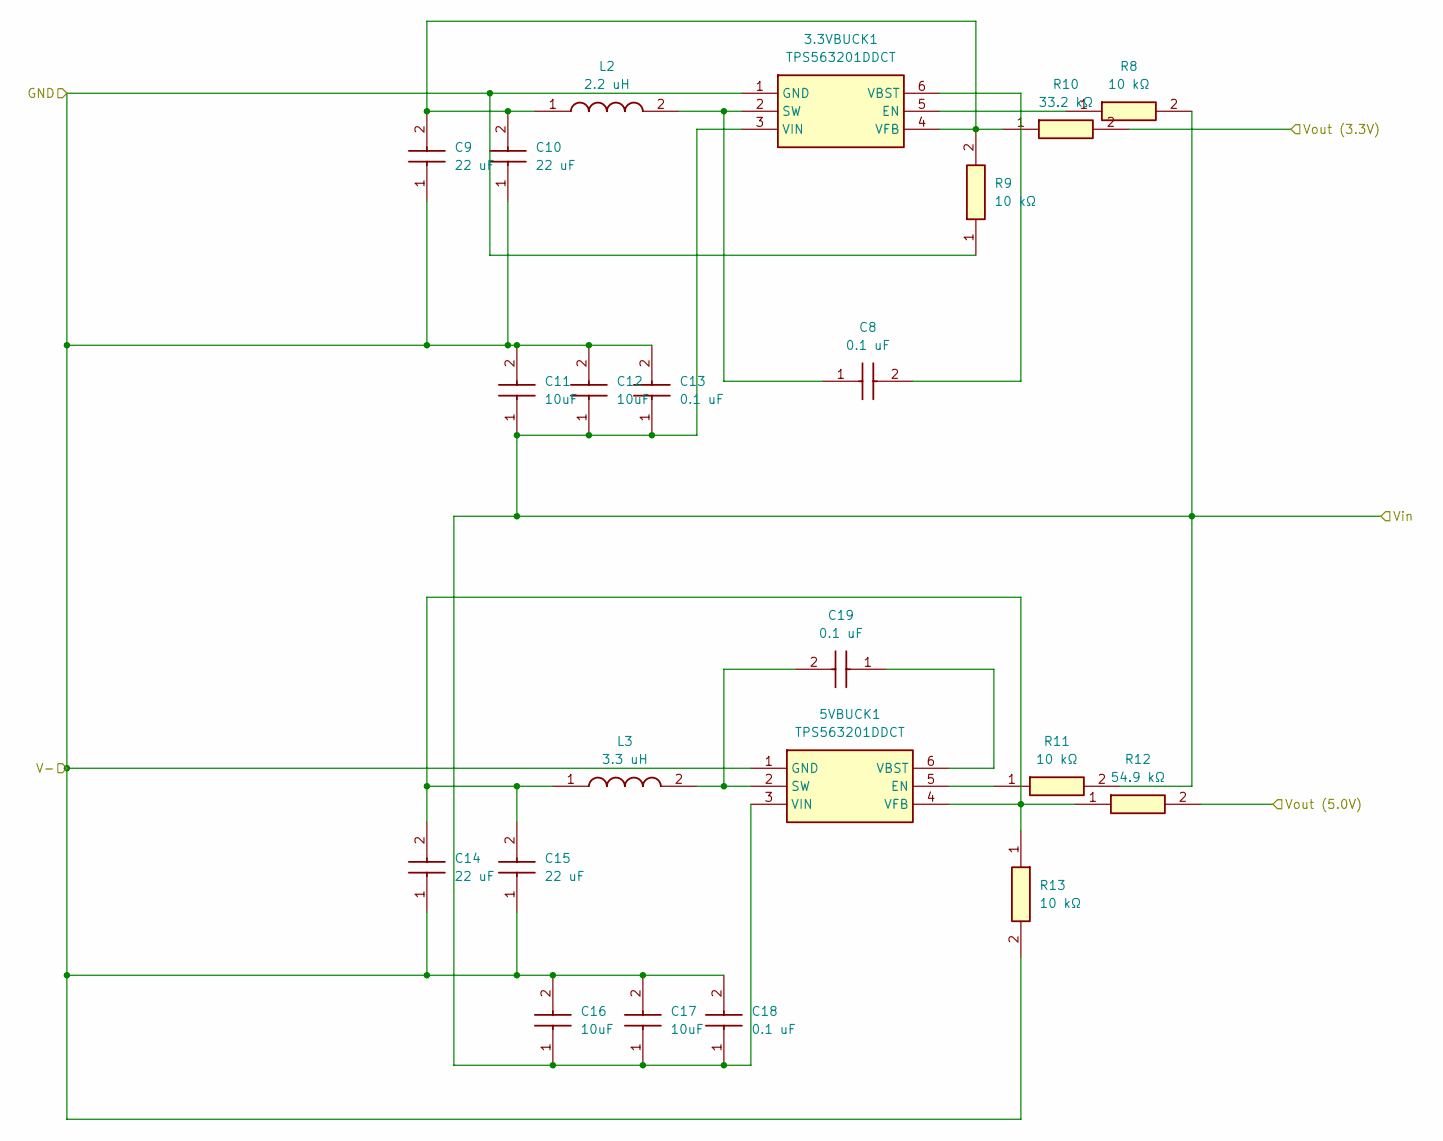
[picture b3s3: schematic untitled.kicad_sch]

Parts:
3.3VBUCK1, 5VBUCK1: TPS563201DDCT; SOT95P280X110-6N; Manufacturer_Part_Number TPS563201DDCT; Mouser Part Number 595-TPS563201DDCT
C8, C13, C18, C19: 0.1 uF; Manufacturer_Part_Number C0603C104K1RACAUTO; Mouser Part Number 80-C0603C104K1RAUTO
C9, C10, C14, C15: 22 uF; CAPC3216X180N; Manufacturer_Part_Number C3216X5R1E226M160AB; Mouser Part Number 810-C3216X5R1E226M
C11, C12, C16, C17: 10uF; Manufacturer_Part_Number GRM188R61E106KA73D; Mouser Part Number 81-GRM188R61E106KA3D
L2: 2.2 uH; DFE2016CKA1R0MP2; Manufacturer_Part_Number DFE2016CKA-2R2M=P2; Mouser Part Number 81-DFE2016CKA2R2M=P2
L3: 3.3 uH; INDC2520X120N; Manufacturer_Part_Number TFM252012ALVA3R3MTAA; Mouser Part Number 810-TFM252012ALVA3R3
R8, R9, R11, R13: 10 kΩ; Manufacturer_Part_Number ERJ-1GJF1002C; Mouser Part Number 667-ERJ-1GJF1002C
R10: 33.2 kΩ; 33.2 kO; Manufacturer_Part_Number ERA-2AEB3322X; Mouser Part Number 667-ERA-2AEB3322X
R12: 54.9 kΩ; Manufacturer_Part_Number ERJ-UP3F5492V

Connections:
3.3V: R10.2; also elsewhere on the board
5V: R12.2; also elsewhere on the board
/BOOST CONVERTER SYSTEM/Vout: 3.3VBUCK1.3 (VIN), 5VBUCK1.3 (VIN), C11.1, C12.1, C13.1, C16.1, C17.1, C18.1, R8.2, R11.2; also elsewhere on the board
Battery #1 V+: 3.3VBUCK1.1 (GND), 5VBUCK1.1 (GND), C9.1, C10.1, C11.2, C12.2, C13.2, C14.1, C15.1, C16.2, C17.2, C18.2, R9.1, R13.2; also elsewhere on the board
unnamed: 3.3VBUCK1.5 (EN), R8.1
unnamed: 3.3VBUCK1.2 (SW), C8.1, L2.2
unnamed: 3.3VBUCK1.6 (VBST), C8.2
unnamed: 3.3VBUCK1.4 (VFB), C9.2, C10.2, L2.1, R9.2, R10.1
unnamed: 5VBUCK1.5 (EN), R11.1
unnamed: 5VBUCK1.2 (SW), C19.2, L3.2
unnamed: 5VBUCK1.6 (VBST), C19.1
unnamed: 5VBUCK1.4 (VFB), C14.2, C15.2, L3.1, R12.1, R13.1

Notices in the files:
Core/Src/stm32f4xx_hal_msp.c:
Copyright (c) 2023 STMicroelectronics.
All rights reserved.
This software is licensed under terms that can be found in the LICENSE file
